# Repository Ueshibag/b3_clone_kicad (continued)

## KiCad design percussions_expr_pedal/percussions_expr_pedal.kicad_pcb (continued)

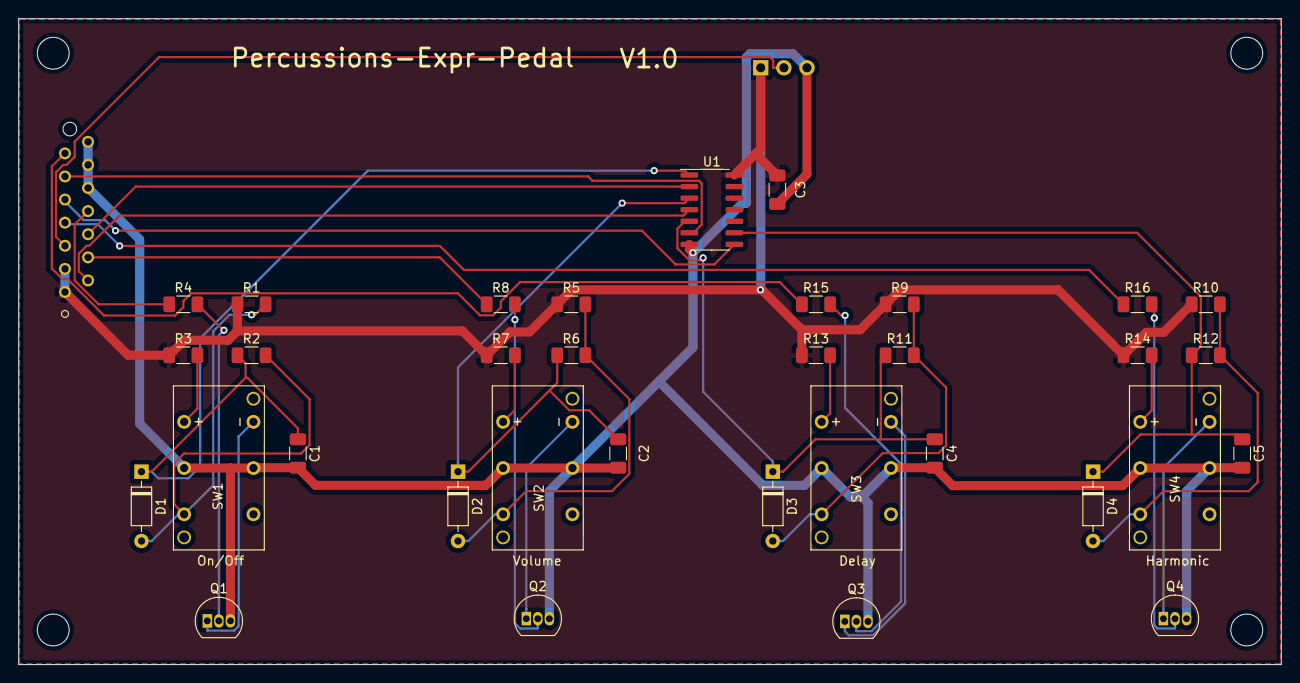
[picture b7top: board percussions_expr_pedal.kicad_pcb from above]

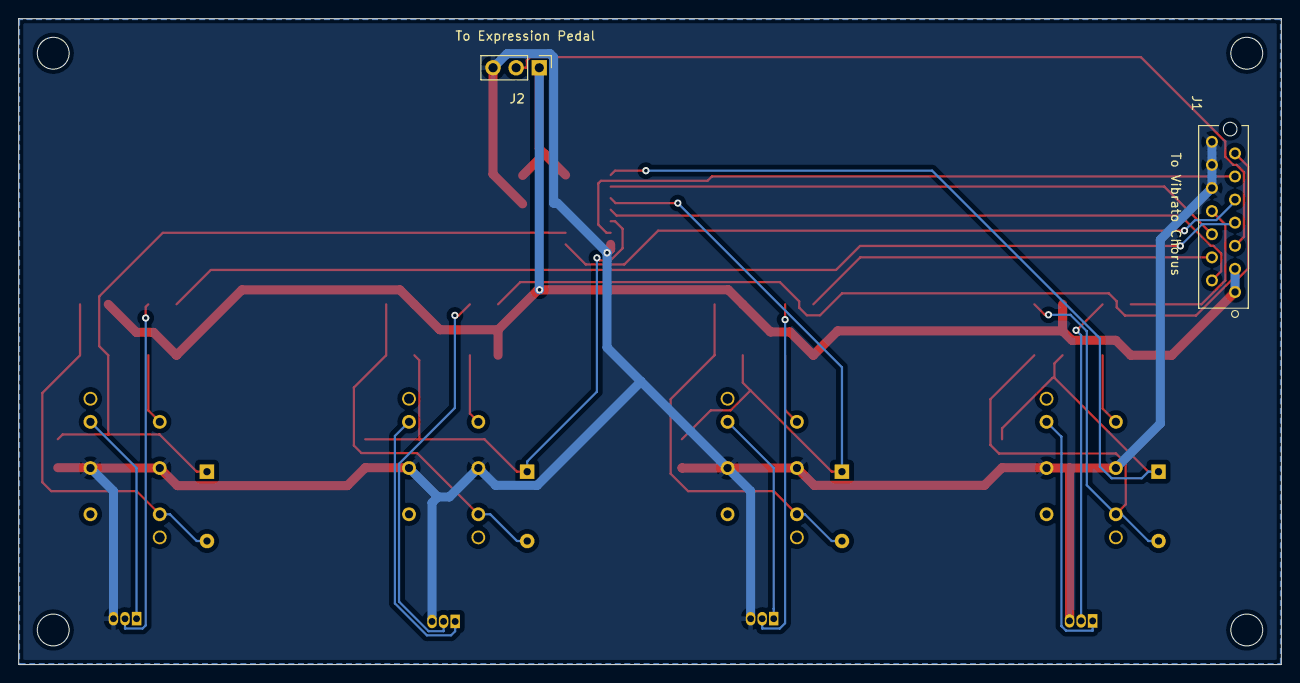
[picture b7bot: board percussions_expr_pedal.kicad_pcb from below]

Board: 2 copper layers, 138.8 x 71.0 mm, 40 parts (2 on the bottom side), 31 nets.

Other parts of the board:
REF1, REF2, REF3, REF4: MountingHole_3.5mm

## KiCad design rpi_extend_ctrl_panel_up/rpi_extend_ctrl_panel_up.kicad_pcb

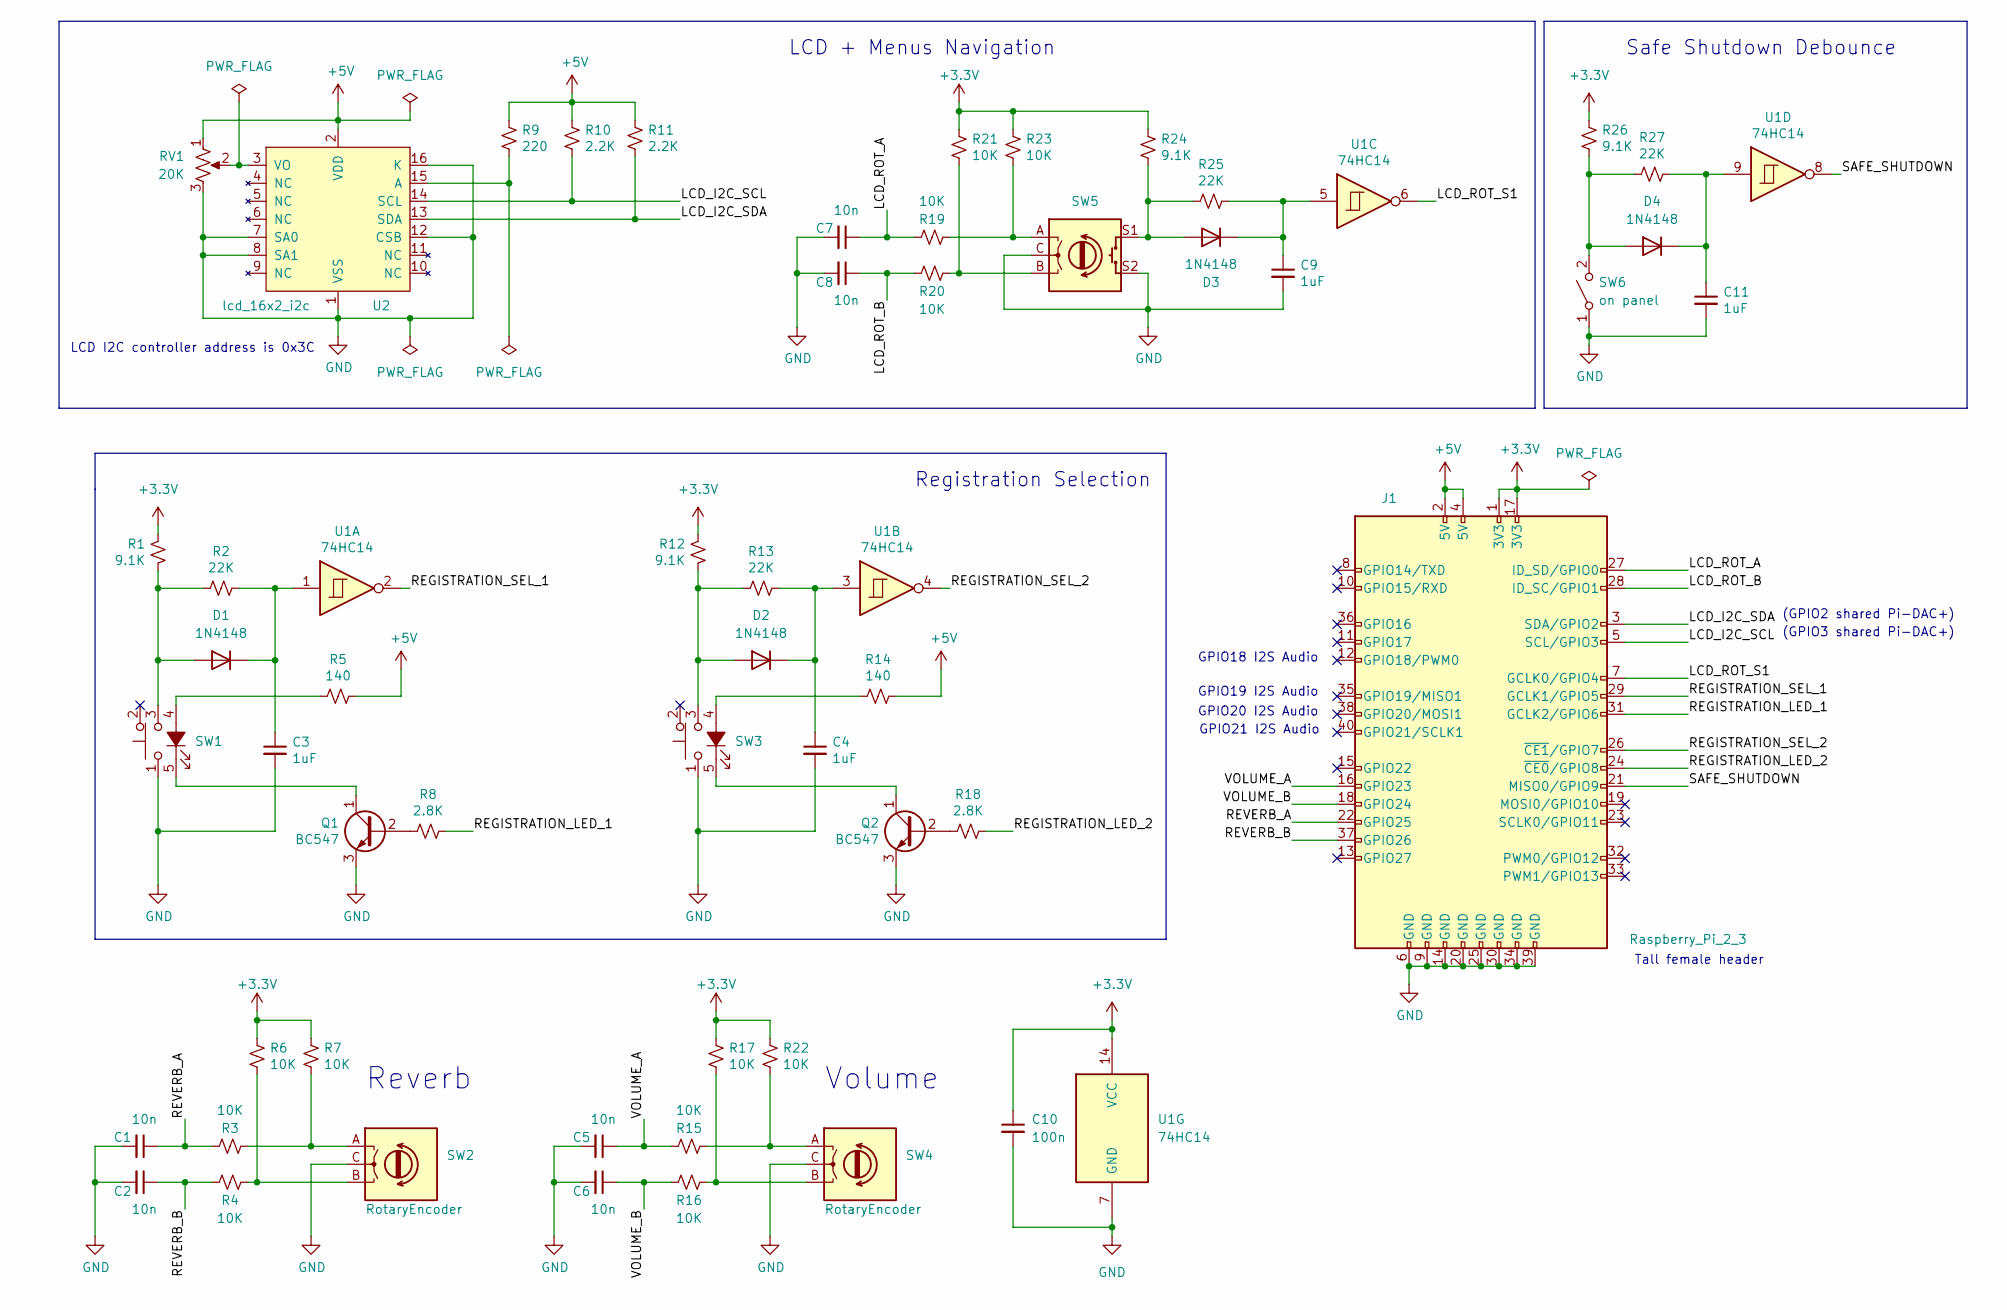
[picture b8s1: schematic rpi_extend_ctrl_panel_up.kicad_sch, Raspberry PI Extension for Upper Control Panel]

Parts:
C1, C2, C5, C6, C7, C8: 10n; C_1206_3216Metric_Pad1.33x1.80mm_HandSolder
C3, C4, C9, C11: 1uF; C_1206_3216Metric_Pad1.33x1.80mm_HandSolder
C10: 100n; C_1206_3216Metric_Pad1.33x1.80mm_HandSolder
D1, D2, D3, D4: 1N4148; D_DO-35_SOD27_P7.62mm_Horizontal
J1: Raspberry_Pi_2_3; PinSocket_2x20_P2.54mm_Vertical
Q1, Q2: BC547; TO-92_Inline
R1, R12, R24, R26: 9.1K; R_1206_3216Metric_Pad1.30x1.75mm_HandSolder
R2, R13, R25, R27: 22K; R_1206_3216Metric_Pad1.30x1.75mm_HandSolder
R3, R4, R6, R7, R15, R16, R17, R19, R20, R21, R22, R23: 10K; R_1206_3216Metric_Pad1.30x1.75mm_HandSolder
R5, R14: 140; R_1206_3216Metric_Pad1.30x1.75mm_HandSolder
R8, R18: 2.8K; R_1206_3216Metric_Pad1.30x1.75mm_HandSolder
R9: 220; R_1206_3216Metric_Pad1.30x1.75mm_HandSolder
R10, R11: 2.2K; R_1206_3216Metric_Pad1.30x1.75mm_HandSolder
RV1: 20K; Potentiometer_Bourns_3386P_Vertical
SW1, SW3: E-SWITCH-SW_Push_LED; 5511MBLKRED
SW2, SW4: RotaryEncoder; RotaryEncoder_Alps_EC11E_Vertical_H20mm
SW5: RotaryEncoder_Switch; RotaryEncoder_Alps_EC11E-Switch_Vertical_H20mm
SW6: on panel; PinHeader_1x02_P2.54mm_Vertical
U1: 74HC14; SOIC-14_3.9x8.7mm_P1.27mm
U2: lcd_16x2_i2c; WC1602A

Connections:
+3V3: C10.1, J1.1 (3V3), J1.17 (3V3), R1.1, R6.1, R7.1, R12.1, R17.1, R21.1, R22.1, R23.1, R24.1, R26.1, U1.14 (VCC)
+5V: J1.2 (5V), J1.4 (5V), R5.1, R9.1, R10.1, R11.1, R14.1, RV1.1, U2.2 (VDD)
/LCD_I2C_SCL: J1.5 (SCL/GPIO3), R10.2, U2.14 (SCL)
/LCD_I2C_SDA: J1.3 (SDA/GPIO2), R11.2, U2.13 (SDA)
/LCD_ROT_A: C7.1, J1.27 (ID_SD/GPIO0), R19.2
/LCD_ROT_B: C8.1, J1.28 (ID_SC/GPIO1), R20.2
/LCD_ROT_S1: J1.7 (GCLK0/GPIO4), U1.6
/REGISTRATION_LED_1: J1.31 (GCLK2/GPIO6), R8.1
/REGISTRATION_LED_2: J1.24 (~CE0/GPIO8), R18.1
/REGISTRATION_SEL_1: J1.29 (GCLK1/GPIO5), U1.2
/REGISTRATION_SEL_2: J1.26 (~CE1/GPIO7), U1.4
/REVERB_A: C1.1, J1.22 (GPIO25), R3.2
/REVERB_B: C2.1, J1.37 (GPIO26), R4.2
/SAFE_SHUTDOWN: J1.21 (MISO0/GPIO9), U1.8
/VOLUME_A: C5.1, J1.16 (GPIO23), R15.2
/VOLUME_B: C6.1, J1.18 (GPIO24), R16.2
GND: C1.2, C2.2, C3.2, C4.2, C5.2, C6.2, C7.2, C8.2, C9.2, C10.2, C11.2, J1.6 (GND), J1.9 (GND), J1.14 (GND), J1.20 (GND), J1.25 (GND), J1.30 (GND), J1.34 (GND), J1.39 (GND), Q1.3 (E), Q2.3 (E), RV1.3, SW1.1, SW2.C, SW3.1, SW4.C, SW5.C, SW5.S2, SW6.1 (A), U1.7 (GND), U1.11, U1.13, U2.1 (VSS), U2.7 (SA0), U2.8 (SA1), U2.12 (CSB), U2.16 (K)
unnamed: C3.1, D1.1 (K), R2.1, U1.1
unnamed: C4.1, D2.1 (K), R13.1, U1.3
unnamed: C9.1, D3.1 (K), R25.1, U1.5
unnamed: C11.1, D4.1 (K), R27.1, U1.9
unnamed: D1.2 (A), R1.2, R2.2, SW1.3
unnamed: D2.2 (A), R12.2, R13.2, SW3.3
unnamed: D3.2 (A), R24.2, R25.2, SW5.S1
unnamed: D4.2 (A), R26.2, R27.2, SW6.2 (B)
unnamed: Q1.1 (C), SW1.5 (K)
unnamed: Q1.2 (B), R8.2
unnamed: Q2.1 (C), SW3.5 (K)
unnamed: Q2.2 (B), R18.2
unnamed: R3.1, R7.2, SW2.A
unnamed: R4.1, R6.2, SW2.B
unnamed: R5.2, SW1.4 (A)
unnamed: R9.2, U2.15 (A)
unnamed: R14.2, SW3.4 (A)
unnamed: R15.1, R22.2, SW4.A
unnamed: R16.1, R17.2, SW4.B
unnamed: R19.1, R23.2, SW5.A
unnamed: R20.1, R21.2, SW5.B
unnamed: RV1.2, U2.3 (VO)

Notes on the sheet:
Tall female header
(GPIO2 shared Pi-DAC+)
Safe Shutdown Debounce
LCD I2C controller address is 0x3C
GPIO21 I2S Audio
Registration Selection
GPIO19 I2S Audio
GPIO18 I2S Audio
Reverb
Volume
(GPIO3 shared Pi-DAC+)
LCD + Menus Navigation
GPIO20 I2S Audio

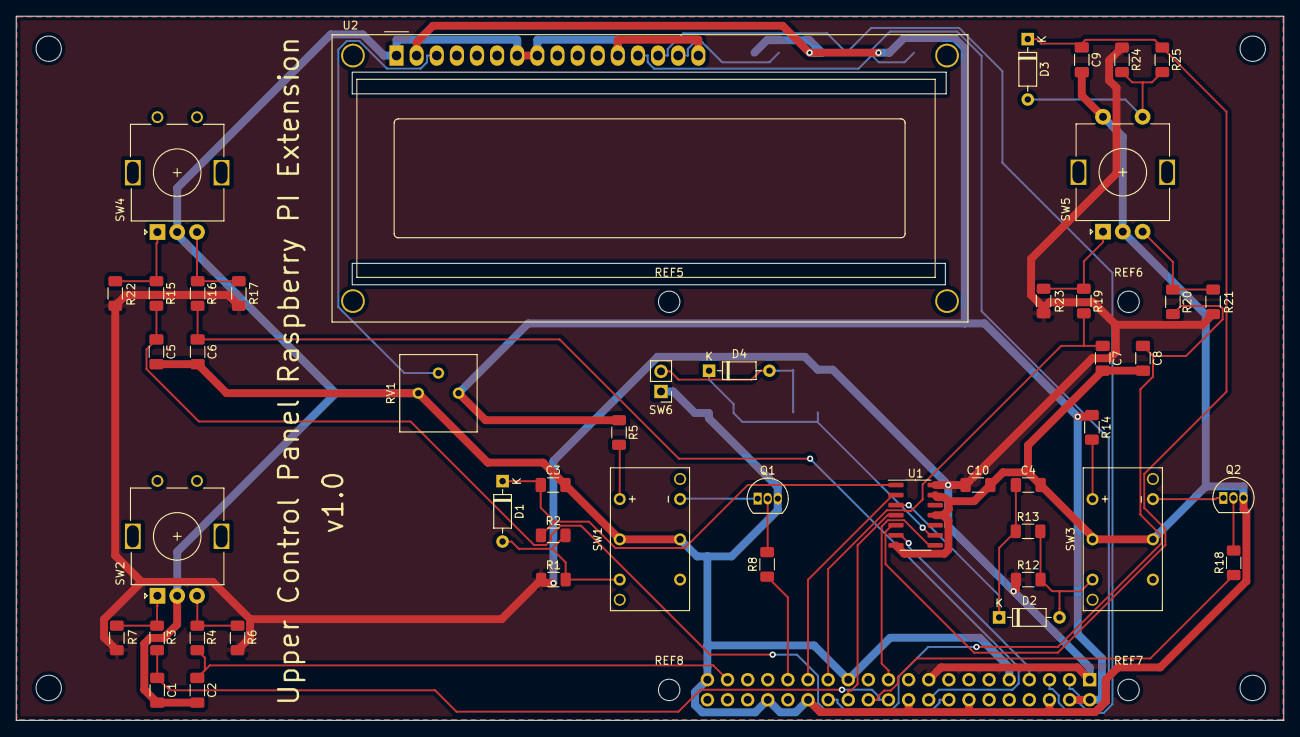
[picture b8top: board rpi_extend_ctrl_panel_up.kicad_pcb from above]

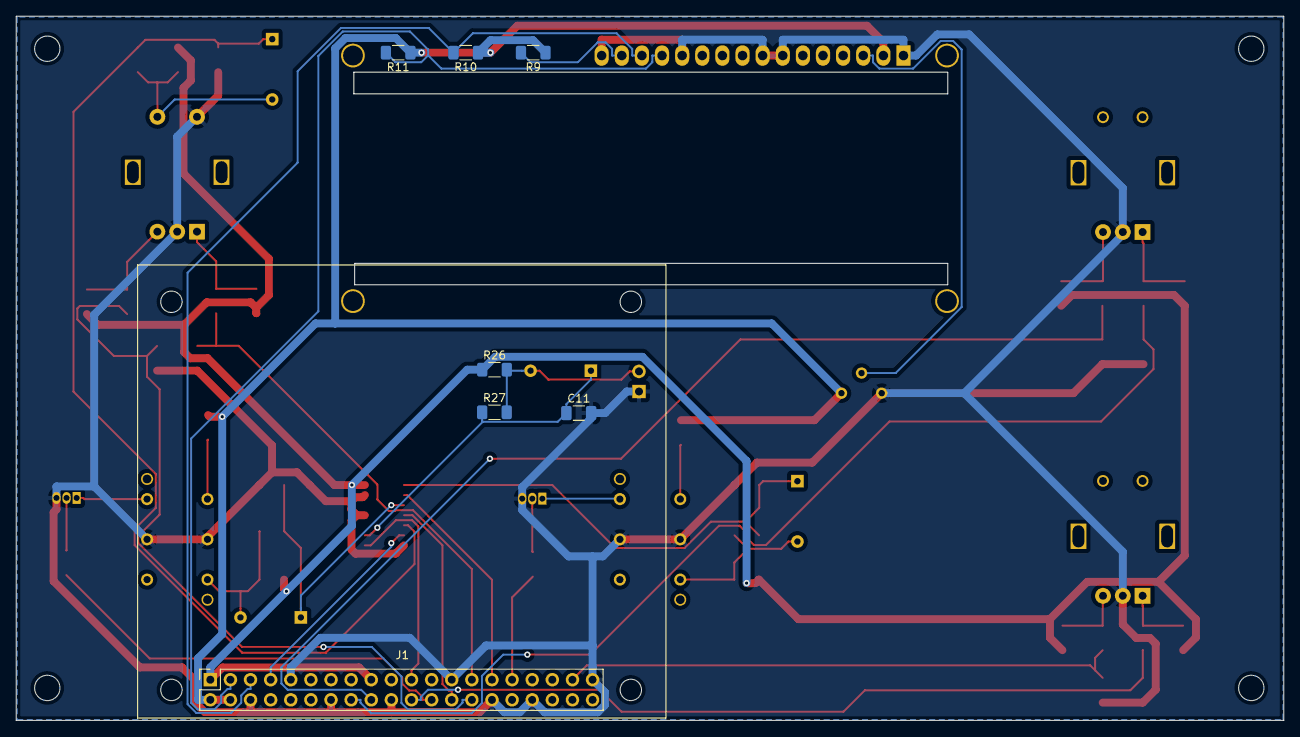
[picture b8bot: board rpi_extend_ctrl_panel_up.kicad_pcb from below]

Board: 2 copper layers, 160.0 x 88.9 mm, 62 parts (7 on the bottom side), 39 nets.

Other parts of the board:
REF1, REF2, REF3, REF4: MountingHole_3.2mm_M3
REF5, REF6, REF7, REF8: MountingHole_2.7mm_M2.5

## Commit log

2022-03-31 My Hammond B3 clone KiCad projects
    KiCad PCBs projects
2022-04-13 Rev 1.1: I2C pull-ups modified
    SDA and SCL external pups (R10 and R11) discarded. Use Raspberry PI internal pups instead. Updating the PCB is not necessary.
2022-04-13 Drawbars Rev 1.1
    On schematics : UP_REG_LED and LO_REG_LED signals were not routed to connectors.
    Connectors pins assignments modified.
    On PCB : Cutting line width increased. PCB width smaller for better drawbars 8 digit visibility when drawbars are pulled to max.
2022-05-09 Rev 1.1
    I2C pull-ups discarded (use RPI I2C GPIO internal pull-ups). R9 value set to 51 Ohm.
2022-05-25 Rotary encoders debounce circuit simplified
    V1.1
2022-11-01 B3 clone overall diagram and volume/reverb
    Kicad overall diagram replaced with Libre Office Draw diagram.
    New volume & reverb KiCad project.
2022-11-01 Raspberry PI UP control panel discarded
2022-11-01 File update
    rpi_up_control_panel discarded.
    volume_reverb description added.
2024-08-04 Volume, reverb, overdrive and safe RPI shutdown controls
    Volume, reverb and overdrive controls are rotary encoders, now located on the same board. The overdrive rotary encoder embeds a push button to shutdown the RPI safely.
2024-08-04 First gitignore file commit
2024-08-04 Ignore folder volume_reverb
2024-08-04 Ignore Gerber folders
2024-08-04 A very small PCB to handle the V/C rotary switch selector
2024-08-04 Files updated to Kicad 8.0
2024-08-04 Info added about new volume_reverb_overdrive board
2024-11-15 New drawbars boards
    The new drawbars PCBs are not chained any more. Every new drawbar PCB is connected to the new mother board.
2024-11-15 The Arduino Nano Every has been discarded.
    This board is connected to the new mother board.
2024-11-15 New Percussions board.
    The Percussion PCB is not connected any more to the Vibrato/Chorus one; it is connected to the new mother board.
2024-11-15 The V/C rotary switch is now connected to the new mother board.
2025-09-19 New organ architecture with mother board
